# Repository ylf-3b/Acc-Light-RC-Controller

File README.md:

# Acc-Light-RC-Controller
Accessories and Light Controller with Arduino for RC Cars

Software for Arduino Micro and Eagle files

Arduino Sketch files (serveral) packed in .zip-file

BreakOut Board is for easyer connecting LEDs in RC-Car

all provided as is

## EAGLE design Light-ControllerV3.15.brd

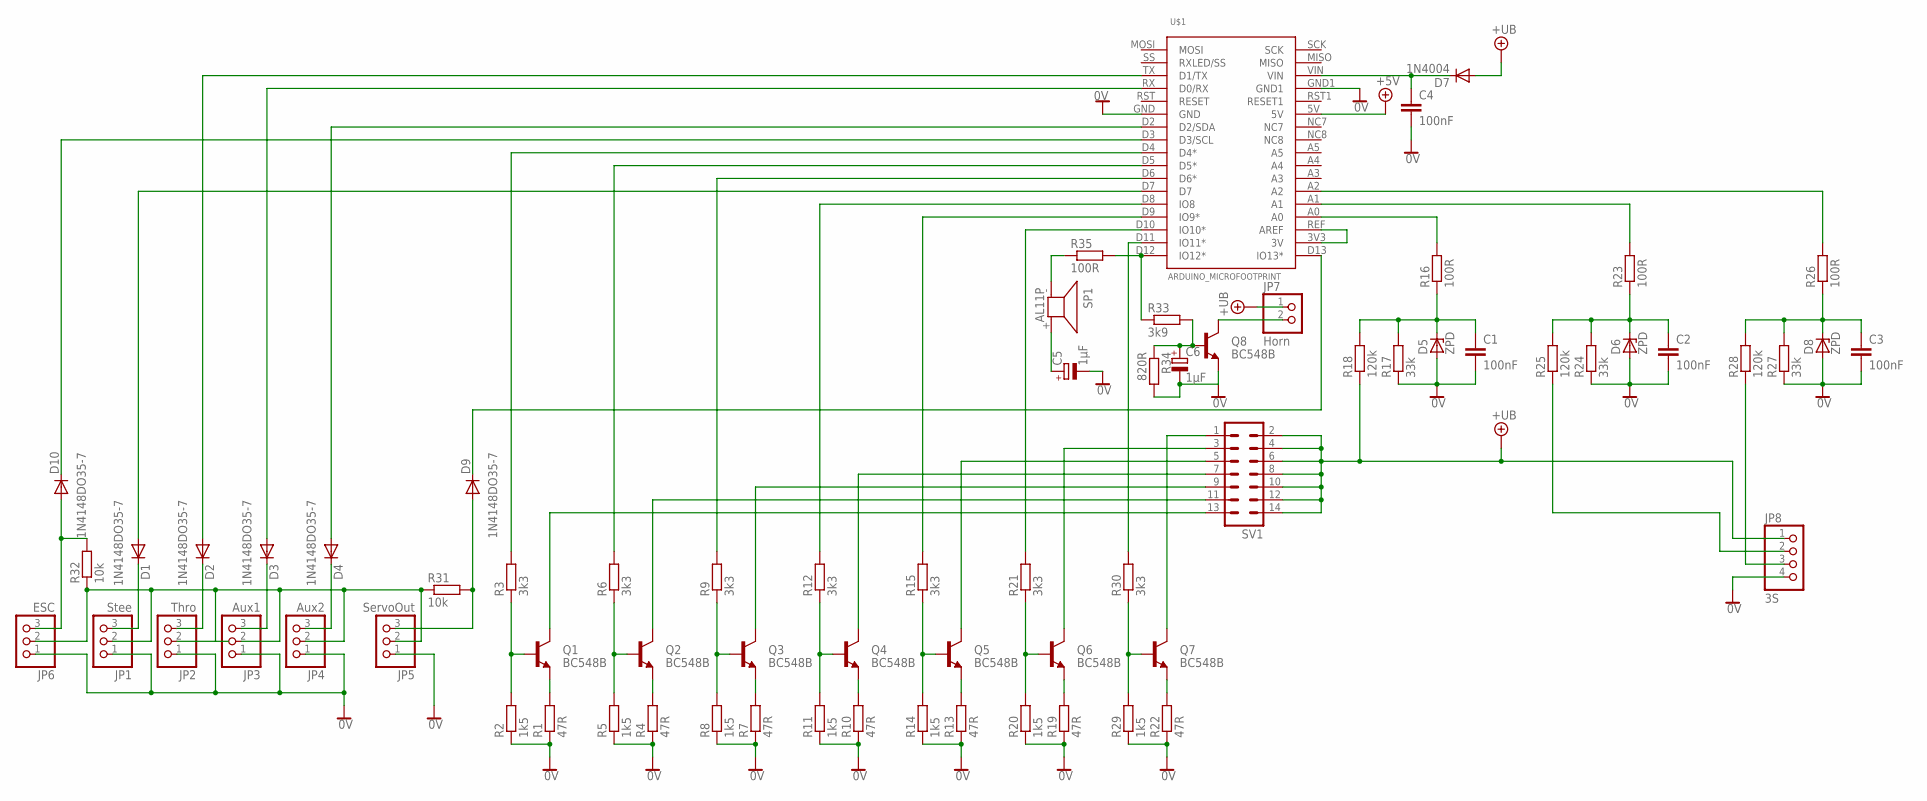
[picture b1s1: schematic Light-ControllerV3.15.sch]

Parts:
C1, C2, C3, C4: 100nF; C050-024X044
C5: 1µF; E5-4
C6: 1µF; E2,5-5
D1, D2, D3, D4, D9, D10: 1N4148DO35-7; DO35-7
D5, D6, D8: ZPD; DO35Z10
D7: 1N4004; DO41-10
JP1: Stee; 1X03
JP2: Thro; 1X03
JP3: Aux1; 1X03
JP4: Aux2; 1X03
JP5: ServoOut; 1X03
JP6: ESC; 1X03
JP7: Horn; 1X02
JP8: 3S; 1X04
Q1, Q2, Q3, Q4, Q5, Q6, Q7, Q8: BC548B; TO92-EBC
R1, R4, R7, R10, R13, R19, R22: 47R; 0204V
R2, R5, R8, R11, R14, R20, R29: 1k5; 0204V
R3, R6, R9, R12, R15, R21, R30: 3k3; 0204V
R16, R23, R26, R35: 100R; 0204/7
R17, R24, R27: 33k; 0204/7
R18, R25, R28: 120k; 0204/7
R31, R32: 10k; 0204V
R33: 3k9; 0204/7
R34: 820R; 0204/7
SP1: AL11P
SV1: ML14
U$1: ARDUINO_MICROFOOTPRINT; ARDUINO-MICRO

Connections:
0V: C1.2, C2.2, C3.2, C4.2, C5.-, C6.-, D5.A, D6.A, D8.A, JP1.1, JP2.1, JP3.1, JP4.1, JP5.1, JP6.1, JP8.4, Q8.E, R1.1, R2.1, R4.1, R5.1, R7.1, R8.1, R10.1, R11.1, R13.1, R14.1, R17.1, R19.1, R20.1, R22.1, R24.1, R27.1, R29.1, R34.2, U$1.GND, U$1.GND1
+5V: U$1.5V
+UB: D7.A, JP7.1, JP8.1, R18.1, SV1.2, SV1.4, SV1.6, SV1.8, SV1.10, SV1.12, SV1.14
+UB1: JP8.2, R25.1
+UB2: JP8.3, R28.1
unnamed: Q1.B, R2.2, R3.1
unnamed: D1.C, JP1.3
unnamed: Q1.E, R1.2
unnamed: Q2.B, R5.2, R6.1
unnamed: Q2.E, R4.2
unnamed: Q3.B, R8.2, R9.1
unnamed: Q3.E, R7.2
unnamed: Q4.B, R11.2, R12.1
unnamed: Q4.E, R10.2
unnamed: Q5.B, R14.2, R15.1
unnamed: Q5.E, R13.2
unnamed: Q1.C, SV1.13
unnamed: Q2.C, SV1.11
unnamed: Q3.C, SV1.9
unnamed: Q4.C, SV1.7
unnamed: Q5.C, SV1.5
unnamed: U$1.3V3 (3V), U$1.REF (AREF)
unnamed: D2.C, JP2.3
unnamed: D3.C, JP3.3
unnamed: D4.C, JP4.3
unnamed: D1.A, U$1.D7
unnamed: JP1.2, JP2.2, JP3.2, JP4.2, JP5.2, JP6.2, R31.1, R32.1
unnamed: D2.A, U$1.TX (D1/TX)
unnamed: D3.A, U$1.RX (D0/RX)
unnamed: D4.A, U$1.D2 (D2/SDA)
unnamed: R3.2, U$1.D4 (D4*)
unnamed: R6.2, U$1.D5 (D5*)
unnamed: R9.2, U$1.D6 (D6*)
unnamed: R12.2, U$1.D8 (IO8)
unnamed: R15.2, U$1.D9 (IO9*)
unnamed: R16.2, U$1.A0
unnamed: C1.1, D5.C, R16.1, R17.2, R18.2
unnamed: Q6.B, R20.2, R21.1
unnamed: Q6.E, R19.2
unnamed: R21.2, U$1.D10 (IO10*)
unnamed: R30.2, U$1.D11 (IO11*)
unnamed: Q7.B, R29.2, R30.1
unnamed: Q7.E, R22.2
unnamed: R23.2, U$1.A1
unnamed: C2.1, D6.C, R23.1, R24.2, R25.2
unnamed: Q6.C, SV1.3
unnamed: C4.1, D7.C, U$1.VIN
unnamed: Q7.C, SV1.1
unnamed: R26.2, U$1.A2
unnamed: C3.1, D8.C, R26.1, R27.2, R28.2
unnamed: R33.1, R35.2, U$1.D12 (IO12*)
unnamed: D9.A, JP5.3, R31.2
unnamed: D9.C, U$1.D13 (IO13*)
unnamed: D10.A, JP6.3, R32.2
unnamed: D10.C, U$1.D3 (D3/SCL)
unnamed: C6.+, Q8.B, R33.2, R34.1
unnamed: JP7.2, Q8.C
unnamed: R35.1, SP1.- (1)
unnamed: C5.+, SP1.+ (2)

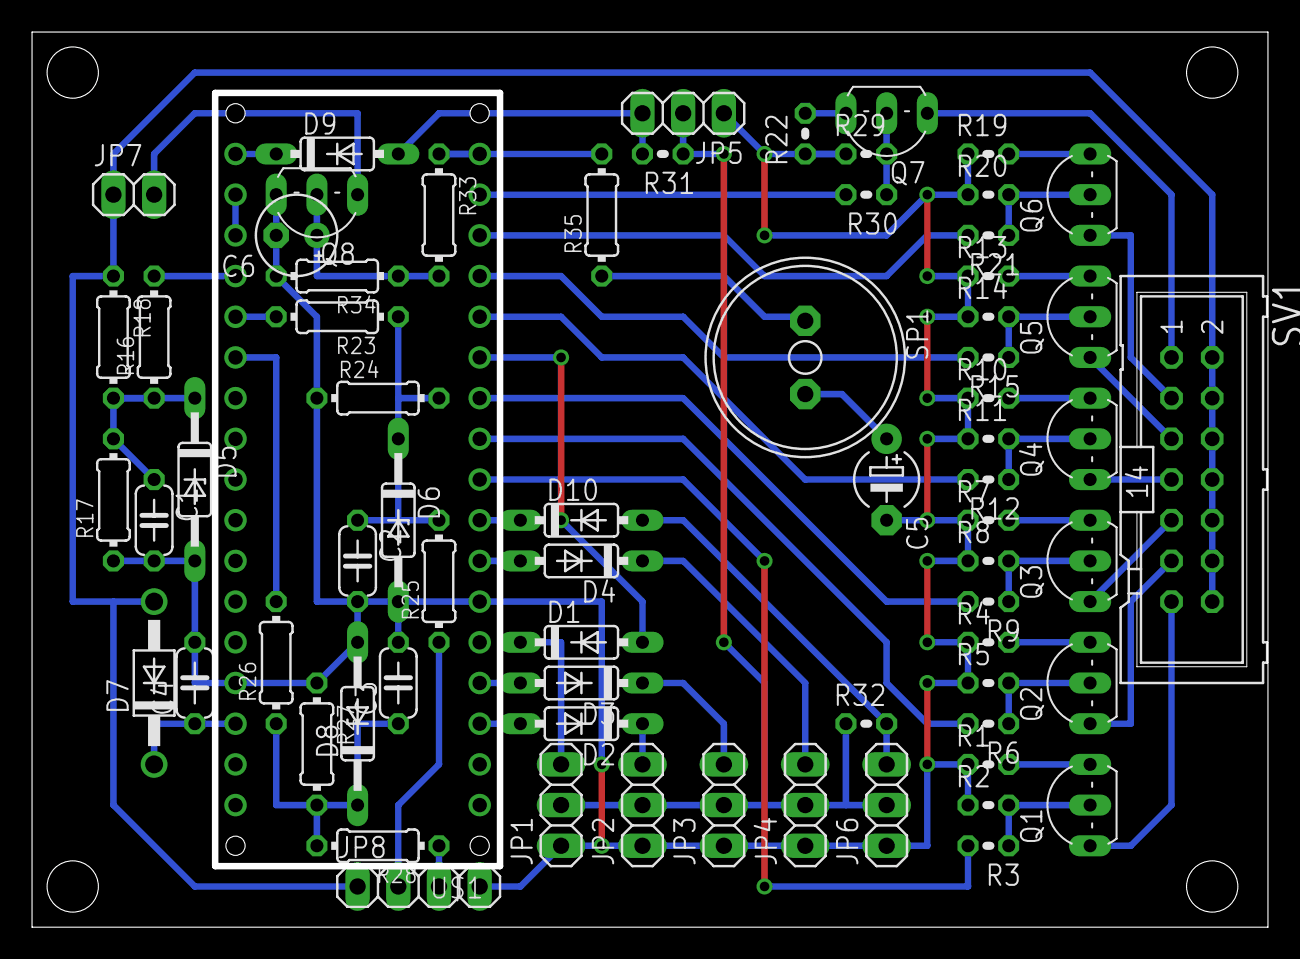
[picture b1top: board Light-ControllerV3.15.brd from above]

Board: 2 copper layers, 76.7 x 55.5 mm, 70 parts (0 on the bottom side), 58 nets.

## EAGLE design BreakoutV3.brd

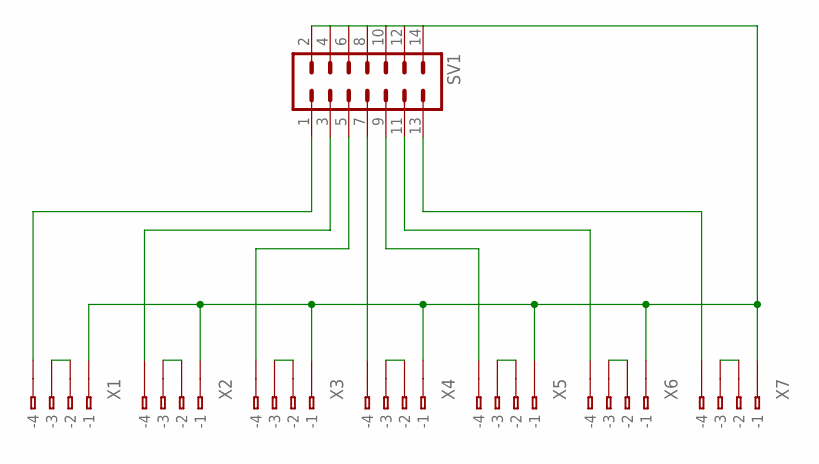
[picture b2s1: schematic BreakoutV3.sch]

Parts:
SV1: ML14
X1, X2, X3, X4, X5, X6, X7: 233-104

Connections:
unnamed: X1.B2 (B-2), X1.B3 (B-3)
unnamed: X2.B2 (B-2), X2.B3 (B-3)
unnamed: X3.B2 (B-2), X3.B3 (B-3)
unnamed: X4.B2 (B-2), X4.B3 (B-3)
unnamed: X5.B2 (B-2), X5.B3 (B-3)
unnamed: X6.B2 (B-2), X6.B3 (B-3)
unnamed: X7.B2 (B-2), X7.B3 (B-3)
unnamed: SV1.2, SV1.4, SV1.6, SV1.8, SV1.10, SV1.12, SV1.14, X1.B1 (B-1), X2.B1 (B-1), X3.B1 (B-1), X4.B1 (B-1), X5.B1 (B-1), X6.B1 (B-1), X7.B1 (B-1)
unnamed: SV1.1, X1.B4 (B-4)
unnamed: SV1.13, X7.B4 (B-4)
unnamed: SV1.3, X2.B4 (B-4)
unnamed: SV1.5, X3.B4 (B-4)
unnamed: SV1.7, X4.B4 (B-4)
unnamed: SV1.9, X5.B4 (B-4)
unnamed: SV1.11, X6.B4 (B-4)

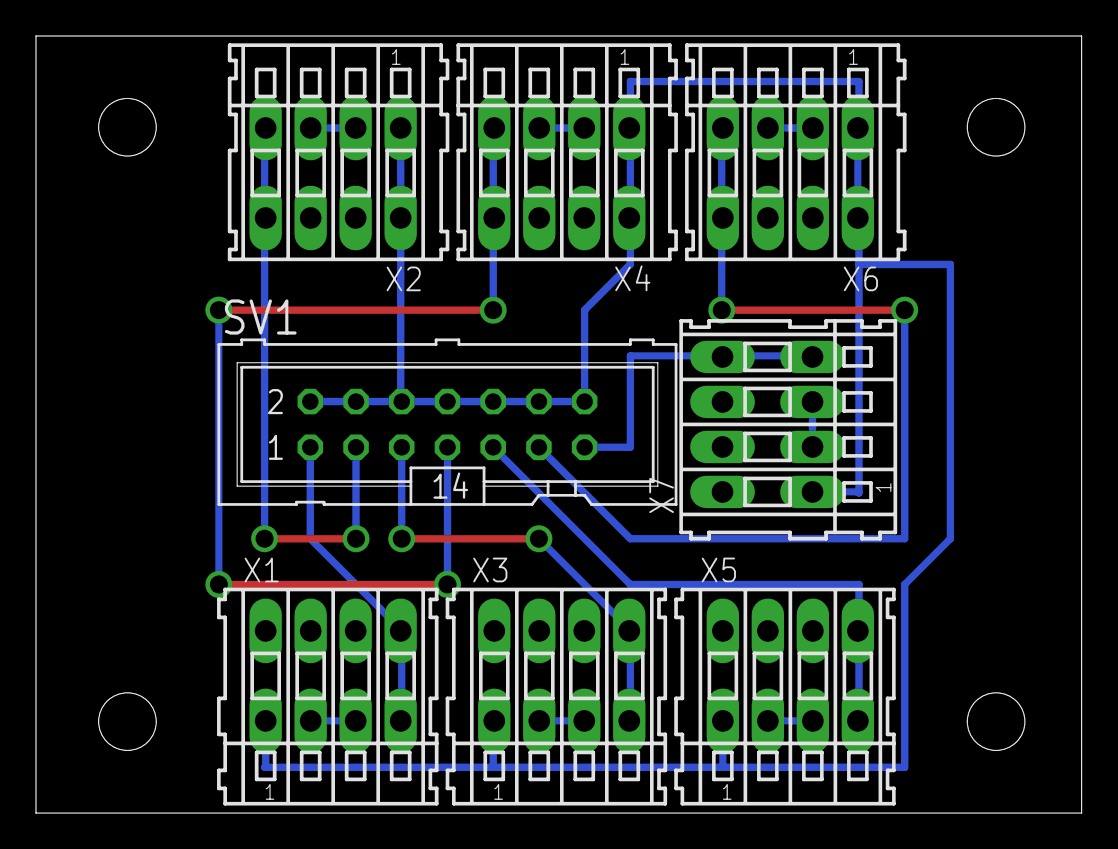
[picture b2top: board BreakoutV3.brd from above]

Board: 2 copper layers, 58.1 x 43.2 mm, 8 parts (0 on the bottom side), 15 nets.

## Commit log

2016-07-30 Add files via upload
    First upload Eagle files and arduino sketch
2016-07-30 Update README.md
    add short explantion
2016-08-01 Delete Light-ControllerV3.15.brd
    missing wire in layout
2016-08-01 Add files via upload
    added missing wire in layout
